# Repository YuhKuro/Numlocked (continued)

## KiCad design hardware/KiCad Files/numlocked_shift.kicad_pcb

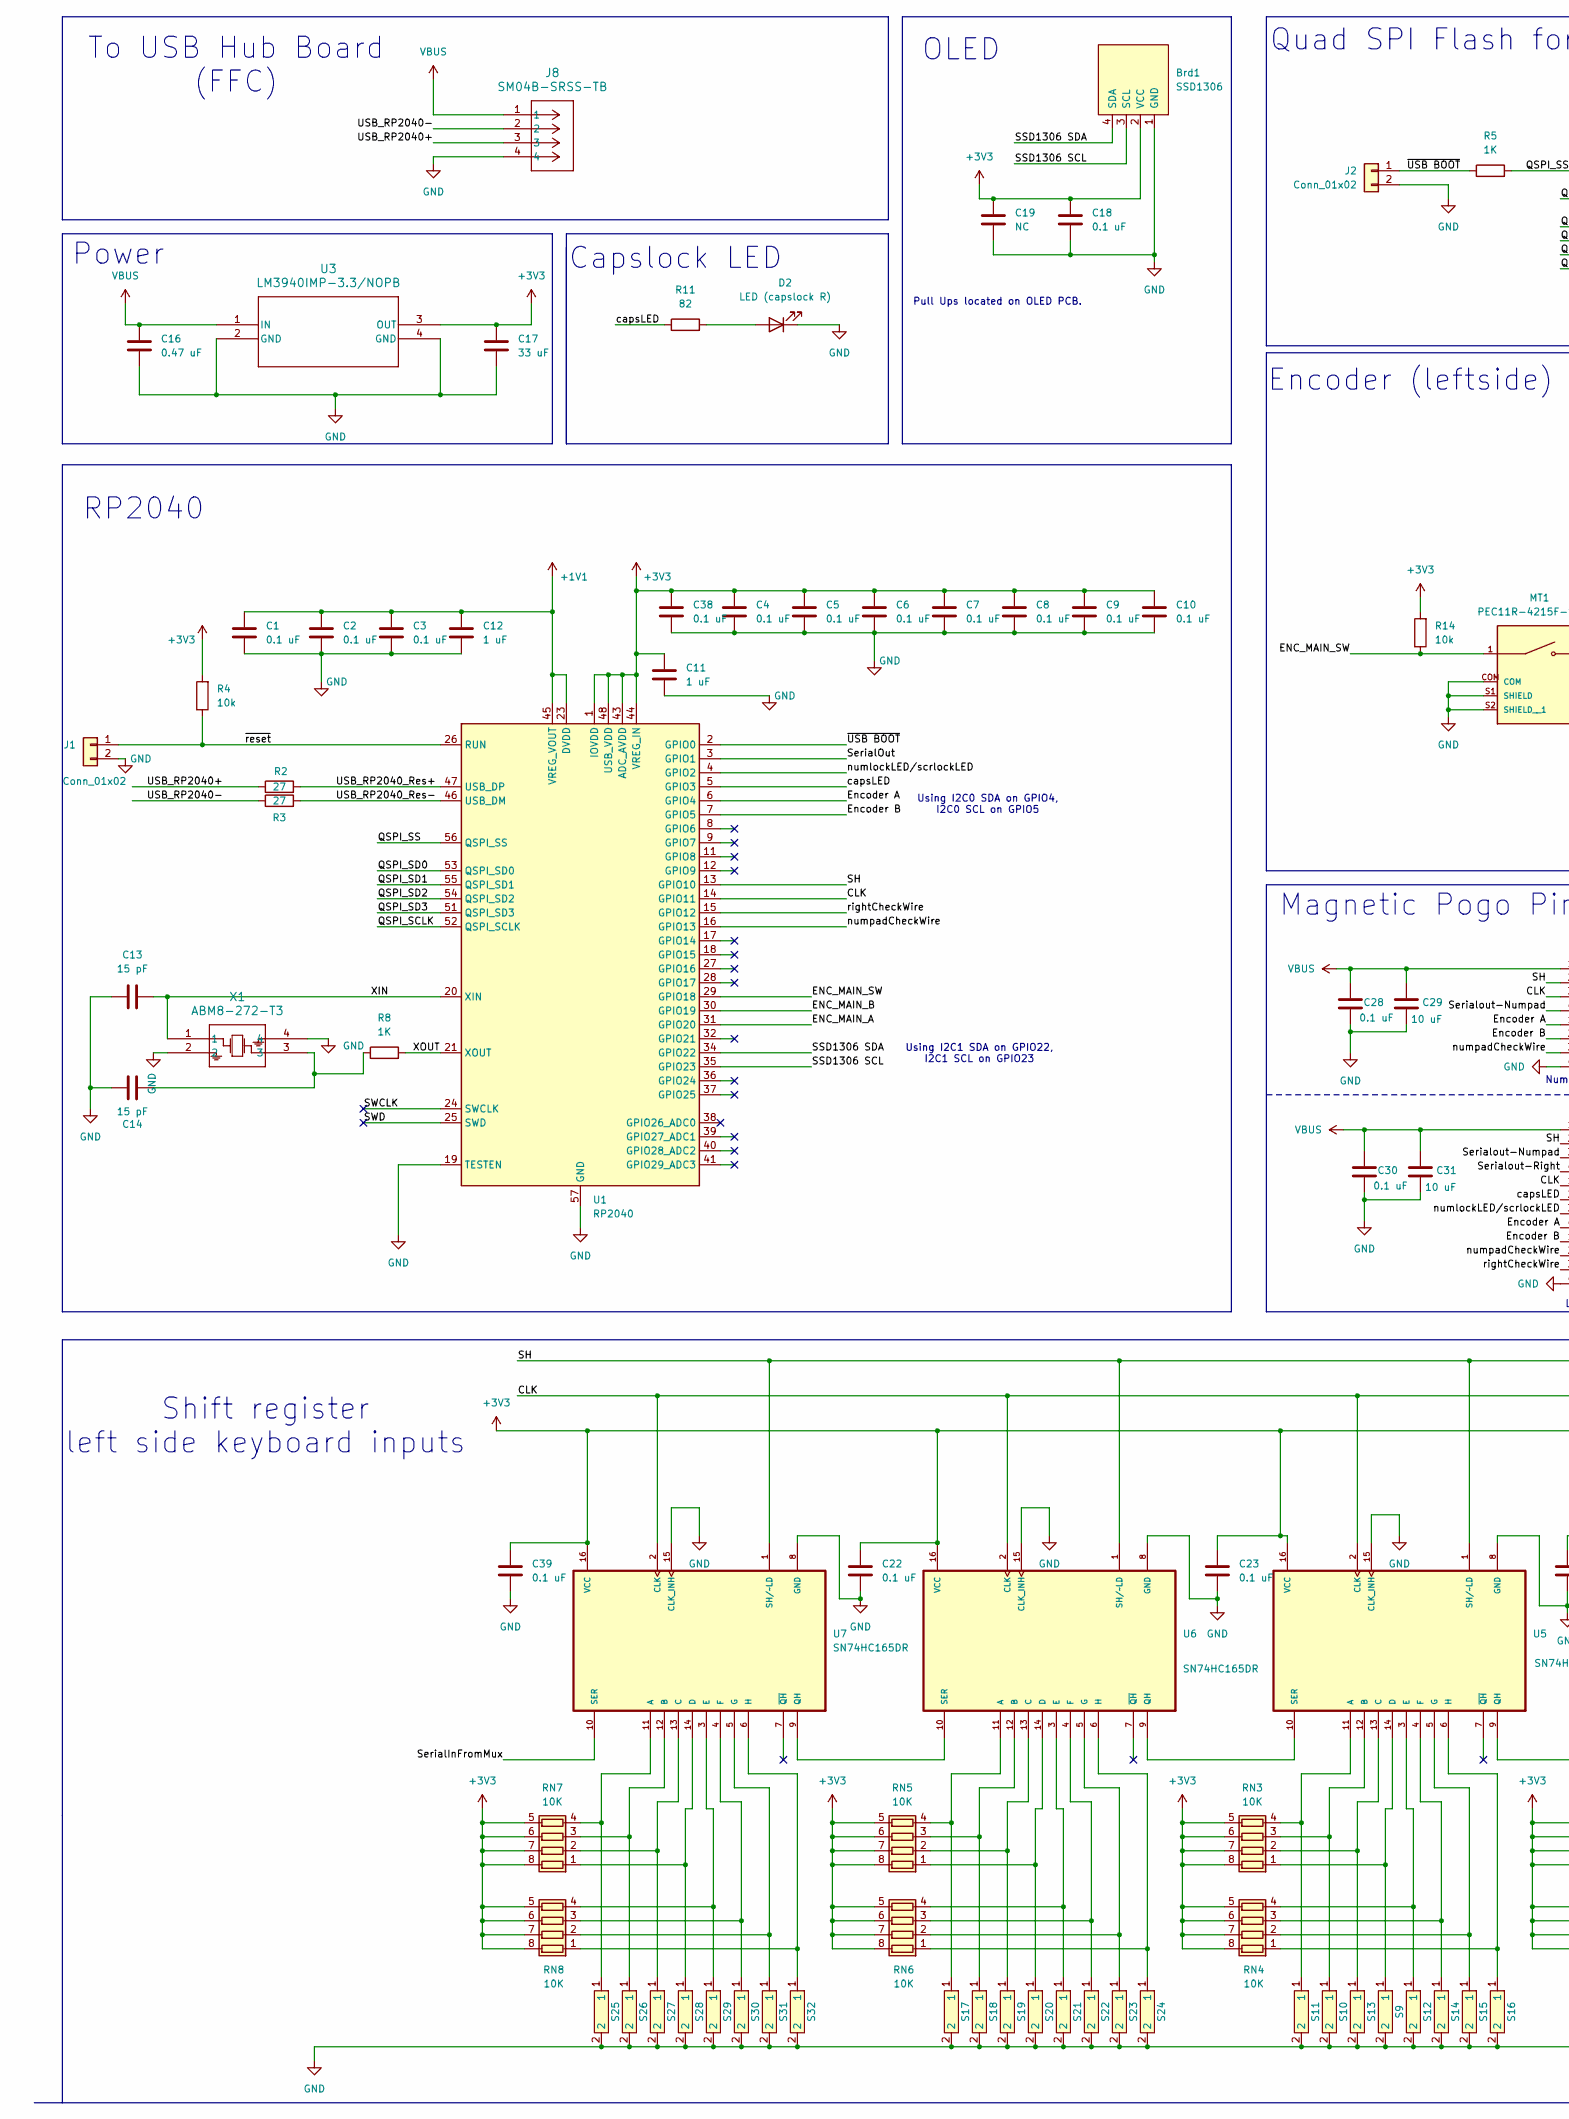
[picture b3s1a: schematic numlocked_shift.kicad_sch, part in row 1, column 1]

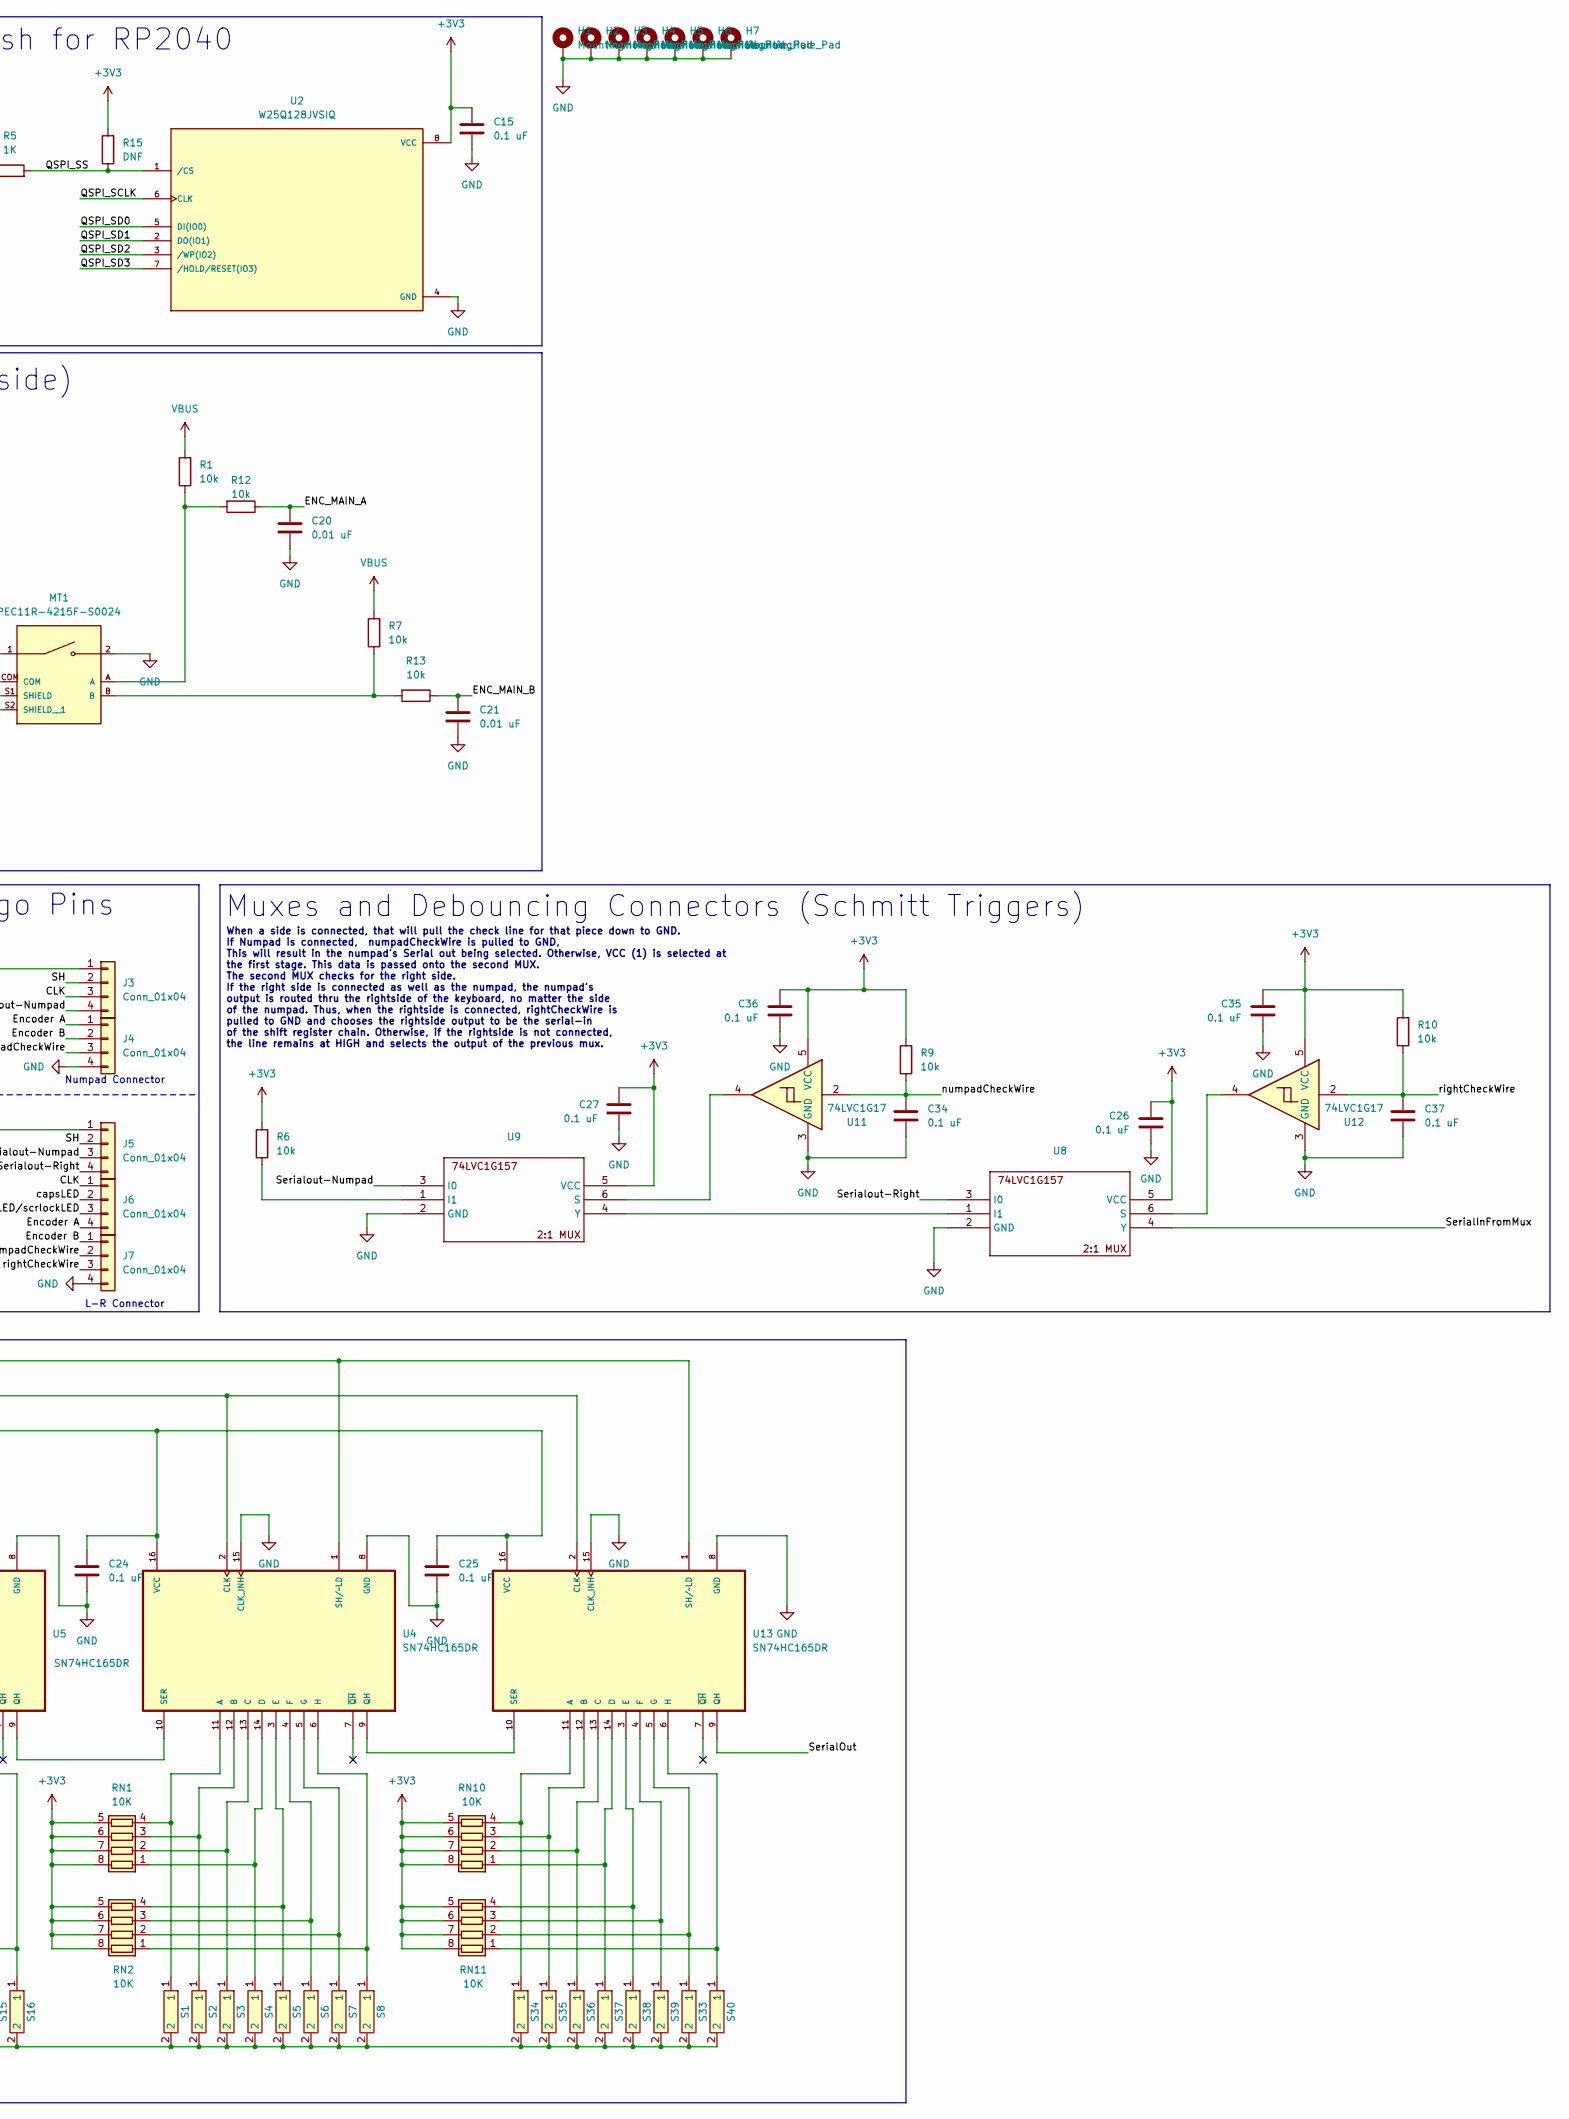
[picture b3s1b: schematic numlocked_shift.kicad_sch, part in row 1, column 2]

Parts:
Brd1: SSD1306; SSD1306-0.91-OLED-4pin-128x32
C1, C2, C3, C4, C5, C6, C7, C8, C9, C10, C18, C22, C23, C24, C25, C26, C27, C28, C30, C34, C35, C36, C37, C38, C39: 0.1 uF; C_0603_1608Metric
C11, C12: 1 uF; C_0603_1608Metric
C13, C14: 15 pF; C_0603_1608Metric
C15: 0.1 uF; C_0603_1608Metric; PARTREV 8/11/2022
C16: 0.47 uF; C_1206_3216Metric
C17: 33 uF; C_1206_3216Metric
C19: NC; C_0603_1608Metric
C20, C21: 0.01 uF; C_0603_1608Metric
C29, C31: 10 uF; C_0603_1608Metric
D2: LED (capslock R); LED_0805_2012Metric_Pad1.15x1.40mm_HandSolder
H1, H2, H3, H4, H5, H6, H7: MountingHole_Pad; MountingHole_2.2mm_M2_Pad
J1, J2: Conn_01x02; PinSocket_1x02_P2.00mm_Vertical
J3, J4, J5, J6, J7: Conn_01x04; Magnetic_Pogo_Pin_4pos
J8: SM04B-SRSS-TB; CONN_SM04B-SRSS-TB_JST
MT1: PEC11R-4215F-S0024; XDCR_PEC11R-4215F-S0024; PARTREV Rev. 09/19
R1, R4, R6, R7, R9, R10, R12, R13, R14: 10k; R_0603_1608Metric
R2, R3: 27; R_0603_1608Metric
R5, R8: 1K; R_0603_1608Metric
R11: 82; R_0603_1608Metric_Pad0.98x0.95mm_HandSolder
R15: DNF; R_0603_1608Metric
RN1, RN2, RN3, RN4, RN5, RN6, RN7, RN8, RN10, RN11: 10K; R_Array_Convex_4x1206
S1, S2, S3, S4, S5, S10, S13, S14, S15, S16, S17, S18, S19, S20, S21, S22, S23, S24, S25, S26, S27, S28, S29, S30, S31, S32, S34, S35, S36, S37, S38, S39, S40: SW_Cherry_Kalih_1.00u
S6: SW_Cherry_Kalih_1.5u
S7: SW_Cherry_Kalih_1.75u
S8: SW_Cherry_Kalih_2.25u
S9, S11, S12: SW_Cherry_Kalih_1.25u
S33: SW_Cherry_Kalih_6.25u
U1: RP2040; QFN-56-1EP_7x7mm_P0.4mm_EP3.2x3.2mm
U2: W25Q128JVSIQ; SOIC127P790X216-8N; PARTREV I
U3: LM3940IMP-3.3/NOPB; SOT-223
U4, U5, U6, U7: SN74HC165DR; SOIC127P600X175-16N
U8, U9: SC-74-6_1.55x2.9mm_P0.95mm
U11, U12: 74LVC1G17; SOT-23-5
U13: SN74HC165DR; SOP-16_3.9x9.9mm_P1.27mm
X1: ABM8-272-T3; Crystal_SMD_Abracon_ABM8AIG-4Pin_3.2x2.5mm

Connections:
+1V1: C1.1, C2.1, C3.1, C12.1, U1.23 (DVDD), U1.45 (VREG_VOUT), U1.50 (DVDD)
+3V3: Brd1.2 (VCC), C4.1, C5.1, C6.1, C7.1, C8.1, C9.1, C10.1, C11.1, C15.1, C17.1, C18.1, C19.1, C22.1, C23.1, C24.1, C25.1, C26.1, C27.1, C35.1, C36.1, C38.1, C39.1, R4.2, R6.2, R9.2, R10.2, R14.2, R15.2, RN1.5 (R4.2), RN1.6 (R3.2), RN1.7 (R2.2), RN1.8 (R1.2), RN2.5 (R4.2), RN2.6 (R3.2), RN2.7 (R2.2), RN2.8 (R1.2), RN3.5 (R4.2), RN3.6 (R3.2), RN3.7 (R2.2), RN3.8 (R1.2), RN4.5 (R4.2), RN4.6 (R3.2), RN4.7 (R2.2), RN4.8 (R1.2), RN5.5 (R4.2), RN5.6 (R3.2), RN5.7 (R2.2), RN5.8 (R1.2), RN6.5 (R4.2), RN6.6 (R3.2), RN6.7 (R2.2), RN6.8 (R1.2), RN7.5 (R4.2), RN7.6 (R3.2), RN7.7 (R2.2), RN7.8 (R1.2), RN8.5 (R4.2), RN8.6 (R3.2), RN8.7 (R2.2), RN8.8 (R1.2), RN10.5 (R4.2), RN10.6 (R3.2), RN10.7 (R2.2), RN10.8 (R1.2), RN11.5 (R4.2), RN11.6 (R3.2), RN11.7 (R2.2), RN11.8 (R1.2), U1.1 (IOVDD), U1.10 (IOVDD), U1.22 (IOVDD), U1.33 (IOVDD), U1.42 (IOVDD), U1.43 (ADC_AVDD), U1.44 (VREG_IN), U1.48 (USB_VDD), U1.49 (IOVDD), U2.8 (VCC), U3.3 (OUT), U4.16 (VCC), U5.16 (VCC), U6.16 (VCC), U7.16 (VCC), U8.5 (VCC), U9.5 (VCC), U11.5 (VCC), U12.5 (VCC), U13.16 (VCC)
/CLK: J3.3, J6.1, U1.14 (GPIO11), U4.2 (CLK), U5.2 (CLK), U6.2 (CLK), U7.2 (CLK), U13.2 (CLK)
/ENC_MAIN_A: C20.1, R12.1, U1.31 (GPIO20)
/ENC_MAIN_B: C21.1, R13.1, U1.30 (GPIO19)
/ENC_MAIN_SW: MT1.1, R14.1, U1.29 (GPIO18)
/Encoder A: J4.1, J6.4, U1.6 (GPIO4)
/Encoder B: J4.2, J7.1, U1.7 (GPIO5)
/QSPI_SCLK: U1.52 (QSPI_SCLK), U2.6 (CLK)
/QSPI_SD0: U1.53 (QSPI_SD0), U2.5 (DI(IO0))
/QSPI_SD1: U1.55 (QSPI_SD1), U2.2 (DO(IO1))
/QSPI_SD2: U1.54 (QSPI_SD2), U2.3 (/WP(IO2))
/QSPI_SD3: U1.51 (QSPI_SD3), U2.7 (/HOLD/RESET(IO3))
/QSPI_SS: R5.2, R15.1, U1.56 (QSPI_SS), U2.1 (/CS)
/SH: J3.2, J5.2, U1.13 (GPIO10), U4.1 (SH/~LD), U5.1 (SH/~LD), U6.1 (SH/~LD), U7.1 (SH/~LD), U13.1 (SH/~LD)
/SSD1306 SCL: Brd1.3 (SCL), U1.35 (GPIO23)
/SSD1306 SDA: Brd1.4 (SDA), U1.34 (GPIO22)
/SWCLK: U1.24 (SWCLK)
/SWD: U1.25 (SWD)
/SerialInFromMux: U7.10 (SER), U8.4 (Y)
/SerialOut: U1.3 (GPIO1), U13.9 (QH)
/Serialout-Numpad: J3.4, J5.3, U9.3 (I0)
/Serialout-Right: J5.4, U8.3 (I0)
/USB_RP2040+: J8.3, R2.1
/USB_RP2040-: J8.2, R3.1
/USB_RP2040_Res+: R2.2, U1.47 (USB_DP)
/USB_RP2040_Res-: R3.2, U1.46 (USB_DM)
/XIN: C13.2, U1.20 (XIN), X1.1
/XOUT: R8.2, U1.21 (XOUT)
/capsLED: J6.2, R11.1, U1.5 (GPIO3)
/numlockLED/scrlockLED: J6.3, U1.4 (GPIO2)
/numpadCheckWire: C34.1, J4.3, J7.2, R9.1, U1.16 (GPIO13), U11.2
/rightCheckWire: C37.1, J7.3, R10.1, U1.15 (GPIO12), U12.2
/~USB BOOT: J2.1, R5.1, U1.2 (GPIO0)
/~reset: J1.1, R4.1, U1.26 (RUN)
GND: Brd1.1 (GND), C1.2, C2.2, C3.2, C4.2, C5.2, C6.2, C7.2, C8.2, C9.2, C10.2, C11.2, C12.2, C13.1, C14.1, C15.2, C16.2, C17.2, C18.2, C19.2, C20.2, C21.2, C22.2, C23.2, C24.2, C25.2, C26.2, C27.2, C28.2, C29.2, C30.2, C31.2, C34.2, C35.2, C36.2, C37.2, C38.2, C39.2, D2.1 (K), H1.1, H2.1, H3.1, H4.1, H5.1, H6.1, H7.1, J1.2, J2.2, J4.4, J7.4, J8.4, MT1.2, MT1.COM, MT1.S1 (SHIELD), MT1.S2 (SHIELD__1), S1.2, S2.2, S3.2, S4.2, S5.2, S6.2, S7.2, S8.2, S9.2, S10.2, S11.2, S12.2, S13.2, S14.2, S15.2, S16.2, S17.2, S18.2, S19.2, S20.2, S21.2, S22.2, S23.2, S24.2, S25.2, S26.2, S27.2, S28.2, S29.2, S30.2, S31.2, S32.2, S33.2, S34.2, S35.2, S36.2, S37.2, S38.2, S39.2, S40.2, U1.19 (TESTEN), U1.57 (GND), U2.4 (GND), U3.2 (GND), U3.4 (GND), U4.8 (GND), U4.15 (CLK_INH), U5.8 (GND), U5.15 (CLK_INH), U6.8 (GND), U6.15 (CLK_INH), U7.8 (GND), U7.15 (CLK_INH), U8.2 (GND), U9.2 (GND), U11.3 (GND), U12.3 (GND), U13.8 (GND), U13.15 (CLK_INH), X1.2, X1.4
unnamed: C14.2, R8.1, X1.3
unnamed: D2.2 (A), R11.2
unnamed: MT1.A, R1.1, R12.2
unnamed: MT1.B, R7.1, R13.2
unnamed: RN1.1 (R1.1), S4.1, U4.14 (D)
unnamed: RN1.2 (R2.1), S3.1, U4.13 (C)
unnamed: RN1.3 (R3.1), S2.1, U4.12 (B)
unnamed: RN1.4 (R4.1), S1.1, U4.11 (A)
unnamed: RN2.1 (R1.1), S8.1, U4.6 (H)
unnamed: RN2.2 (R2.1), S7.1, U4.5 (G)
unnamed: RN2.3 (R3.1), S6.1, U4.4 (F)
unnamed: RN2.4 (R4.1), S5.1, U4.3 (E)
unnamed: RN3.1 (R1.1), S9.1, U5.14 (D)
unnamed: RN3.2 (R2.1), S13.1, U5.13 (C)
unnamed: RN3.3 (R3.1), S10.1, U5.12 (B)
unnamed: RN3.4 (R4.1), S11.1, U5.11 (A)
unnamed: RN4.1 (R1.1), S16.1, U5.6 (H)
unnamed: RN4.2 (R2.1), S15.1, U5.5 (G)
unnamed: RN4.3 (R3.1), S14.1, U5.4 (F)
unnamed: RN4.4 (R4.1), S12.1, U5.3 (E)
unnamed: RN5.1 (R1.1), S20.1, U6.14 (D)
unnamed: RN5.2 (R2.1), S19.1, U6.13 (C)
unnamed: RN5.3 (R3.1), S18.1, U6.12 (B)
unnamed: RN5.4 (R4.1), S17.1, U6.11 (A)
unnamed: RN6.1 (R1.1), S24.1, U6.6 (H)
unnamed: RN6.2 (R2.1), S23.1, U6.5 (G)
unnamed: RN6.3 (R3.1), S22.1, U6.4 (F)
unnamed: RN6.4 (R4.1), S21.1, U6.3 (E)
unnamed: RN7.1 (R1.1), S28.1, U7.14 (D)
unnamed: RN7.2 (R2.1), S27.1, U7.13 (C)
unnamed: RN7.3 (R3.1), S26.1, U7.12 (B)
unnamed: RN7.4 (R4.1), S25.1, U7.11 (A)
unnamed: RN8.1 (R1.1), S32.1, U7.6 (H)
unnamed: RN8.2 (R2.1), S31.1, U7.5 (G)
unnamed: RN8.3 (R3.1), S30.1, U7.4 (F)
unnamed: RN8.4 (R4.1), S29.1, U7.3 (E)
unnamed: RN10.1 (R1.1), S37.1, U13.14 (D)
unnamed: RN10.2 (R2.1), S36.1, U13.13 (C)
unnamed: RN10.3 (R3.1), S35.1, U13.12 (B)
unnamed: RN10.4 (R4.1), S34.1, U13.11 (A)
unnamed: RN11.1 (R1.1), S40.1, U13.6 (H)
unnamed: RN11.2 (R2.1), S33.1, U13.5 (G)
unnamed: RN11.3 (R3.1), S39.1, U13.4 (F)
unnamed: RN11.4 (R4.1), S38.1, U13.3 (E)
unnamed: U4.10 (SER), U5.9 (QH)
unnamed: U5.10 (SER), U6.9 (QH)
unnamed: U6.10 (SER), U7.9 (QH)
unnamed: U8.1 (I1), U9.4 (Y)
unnamed: U8.6 (S), U12.4
unnamed: R6.1, U9.1 (I1)
unnamed: U9.6 (S), U11.4
unnamed: U4.9 (QH), U13.10 (SER)
VBUS: C16.1, C28.1, C29.1, C30.1, C31.1, J3.1, J5.1, J8.1, R1.2, R7.2, U3.1 (IN)

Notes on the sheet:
When a side is connected, that will pull the check line for that piece down to GND. If Numpad is connected, numpadCheckWire is pulled to GND, This will result in the numpad's Serial out being selected. Otherwise, VCC (1) is selected at the first stage. This data is passed onto the second MUX. The s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
Power
L-R Connector
Using I2C1 SDA on GPIO22, I2C1 SCL on GPIO23
Quad SPI Flash for RP2040
Muxes and Debouncing Connectors (Schmitt Triggers)
Using I2C0 SDA on GPIO4, I2C0 SCL on GPIO5
Numpad Connector
OLED
Capslock LED
Pull Ups located on OLED PCB.
Shift register left side keyboard inputs
RP2040
Encoder (leftside)
To USB Hub Board (FFC)
Magnetic Pogo Pins

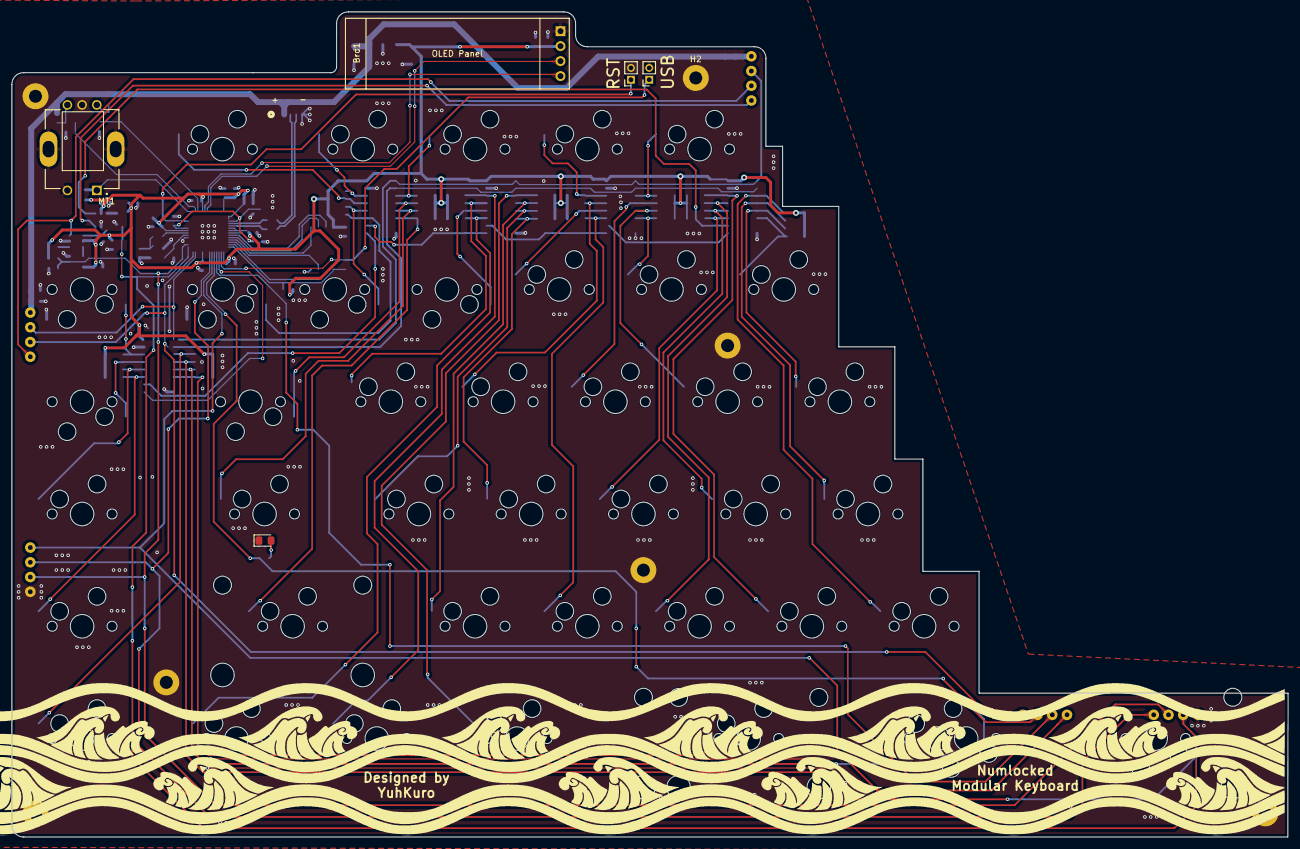
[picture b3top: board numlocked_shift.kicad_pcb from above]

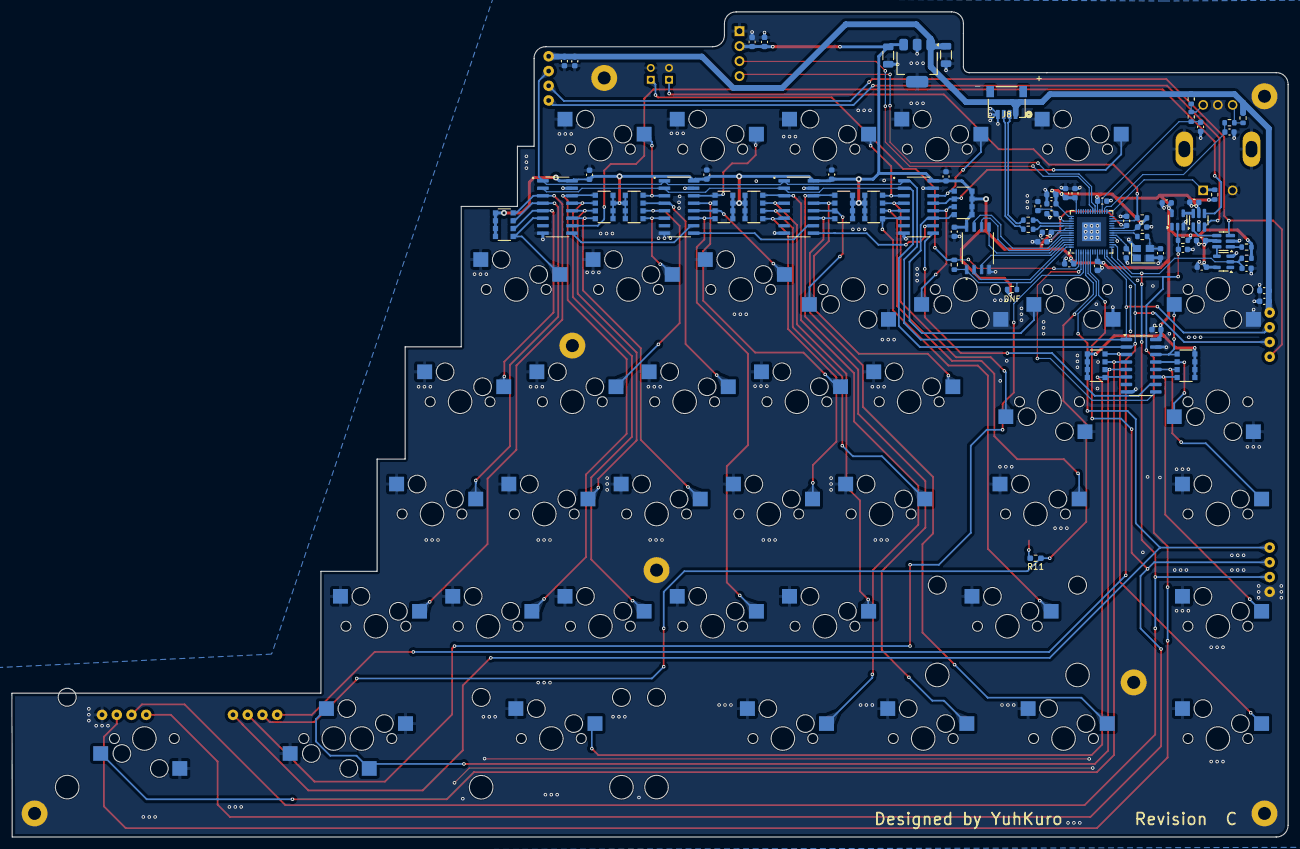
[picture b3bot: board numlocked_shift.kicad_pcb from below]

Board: 4 copper layers, 216.5 x 140.0 mm, 133 parts (78 on the bottom side), 87 nets.

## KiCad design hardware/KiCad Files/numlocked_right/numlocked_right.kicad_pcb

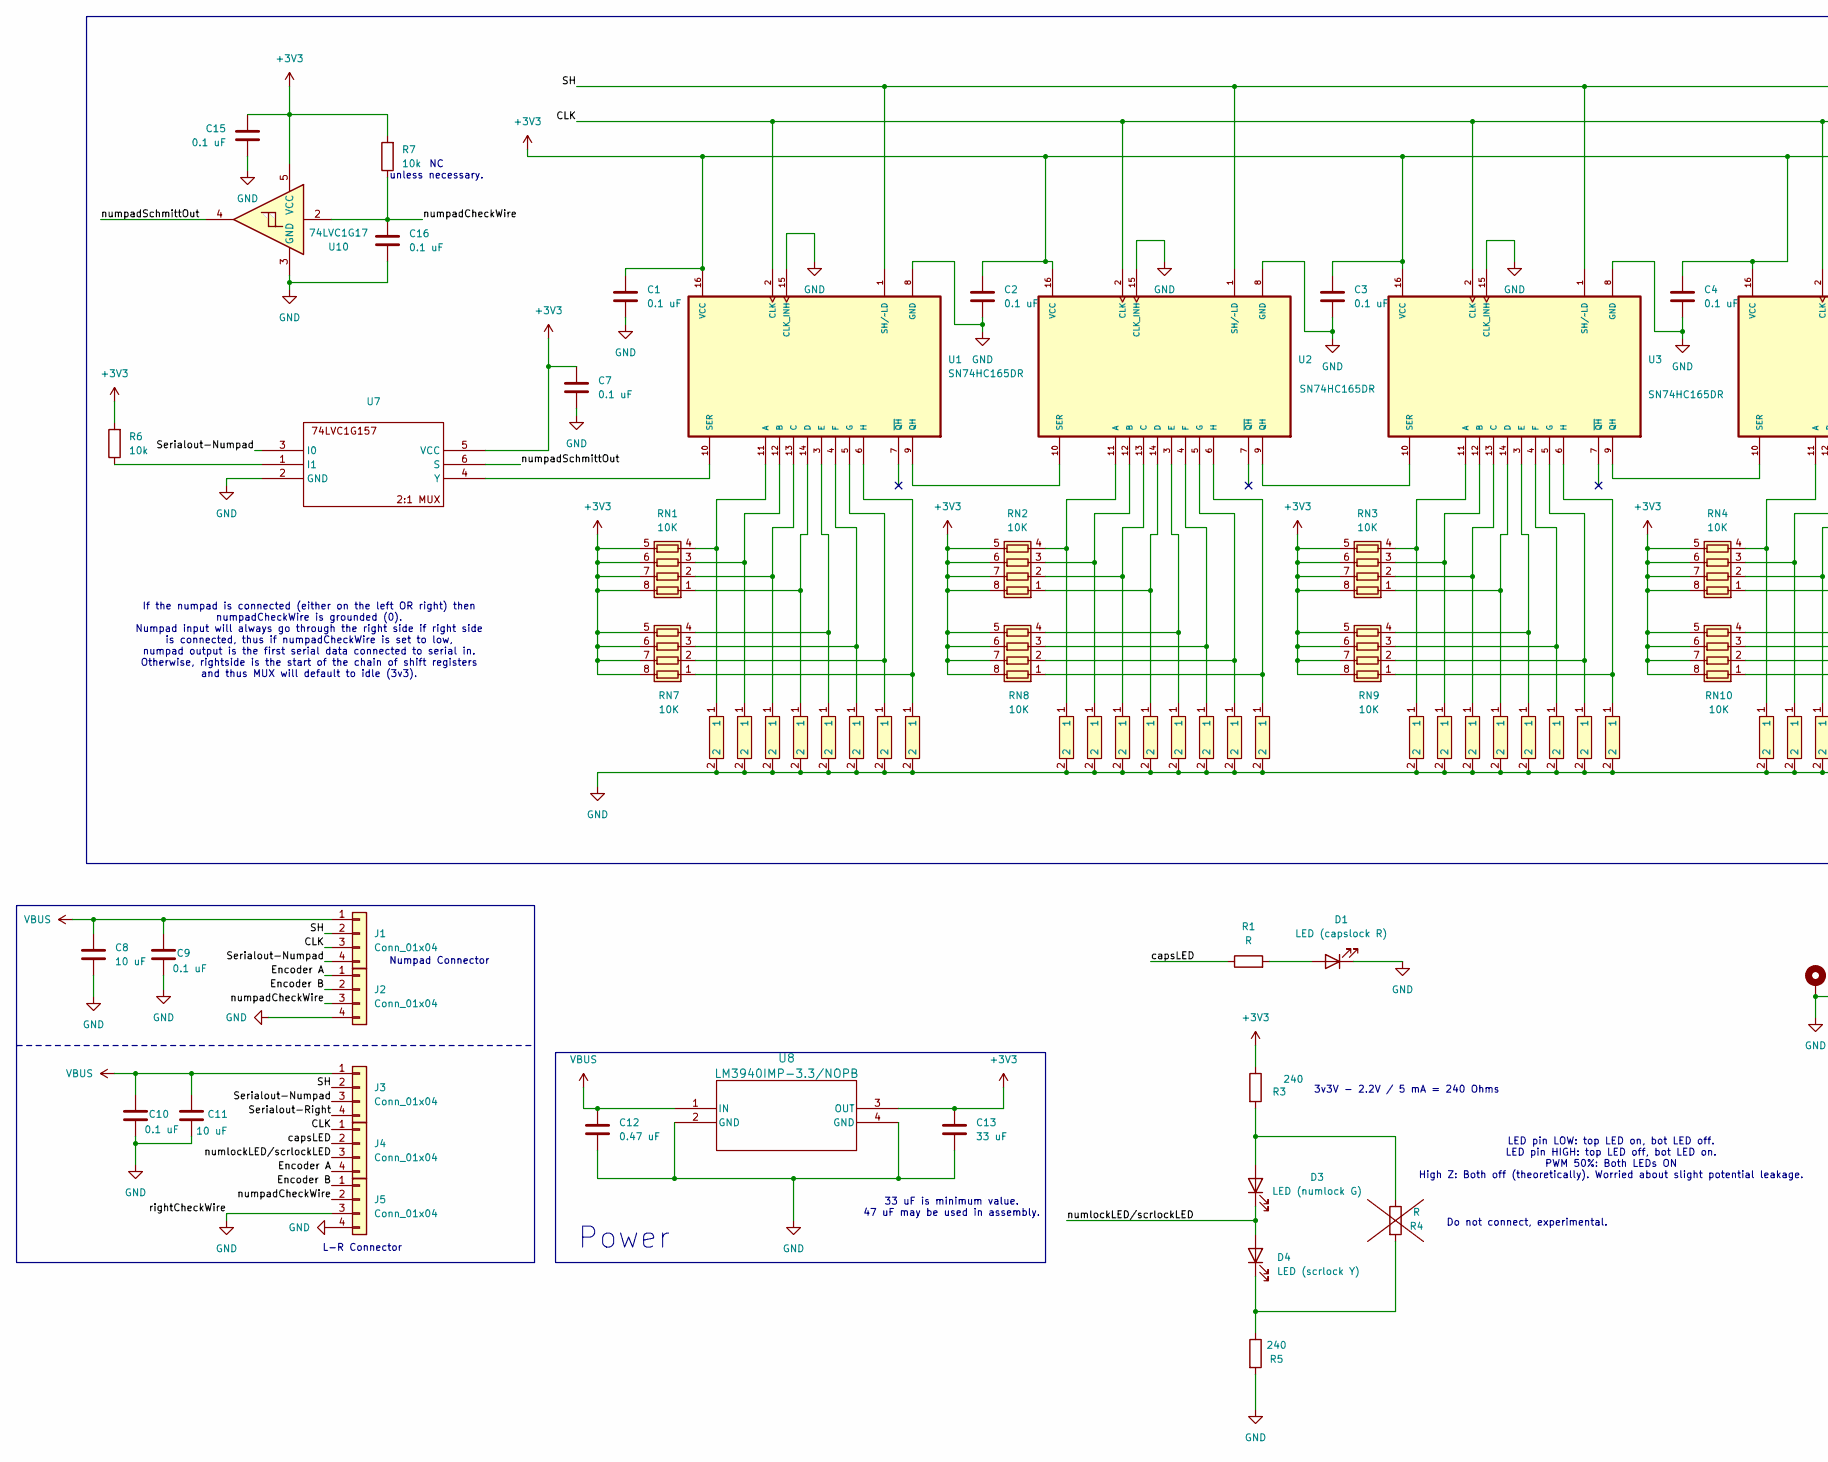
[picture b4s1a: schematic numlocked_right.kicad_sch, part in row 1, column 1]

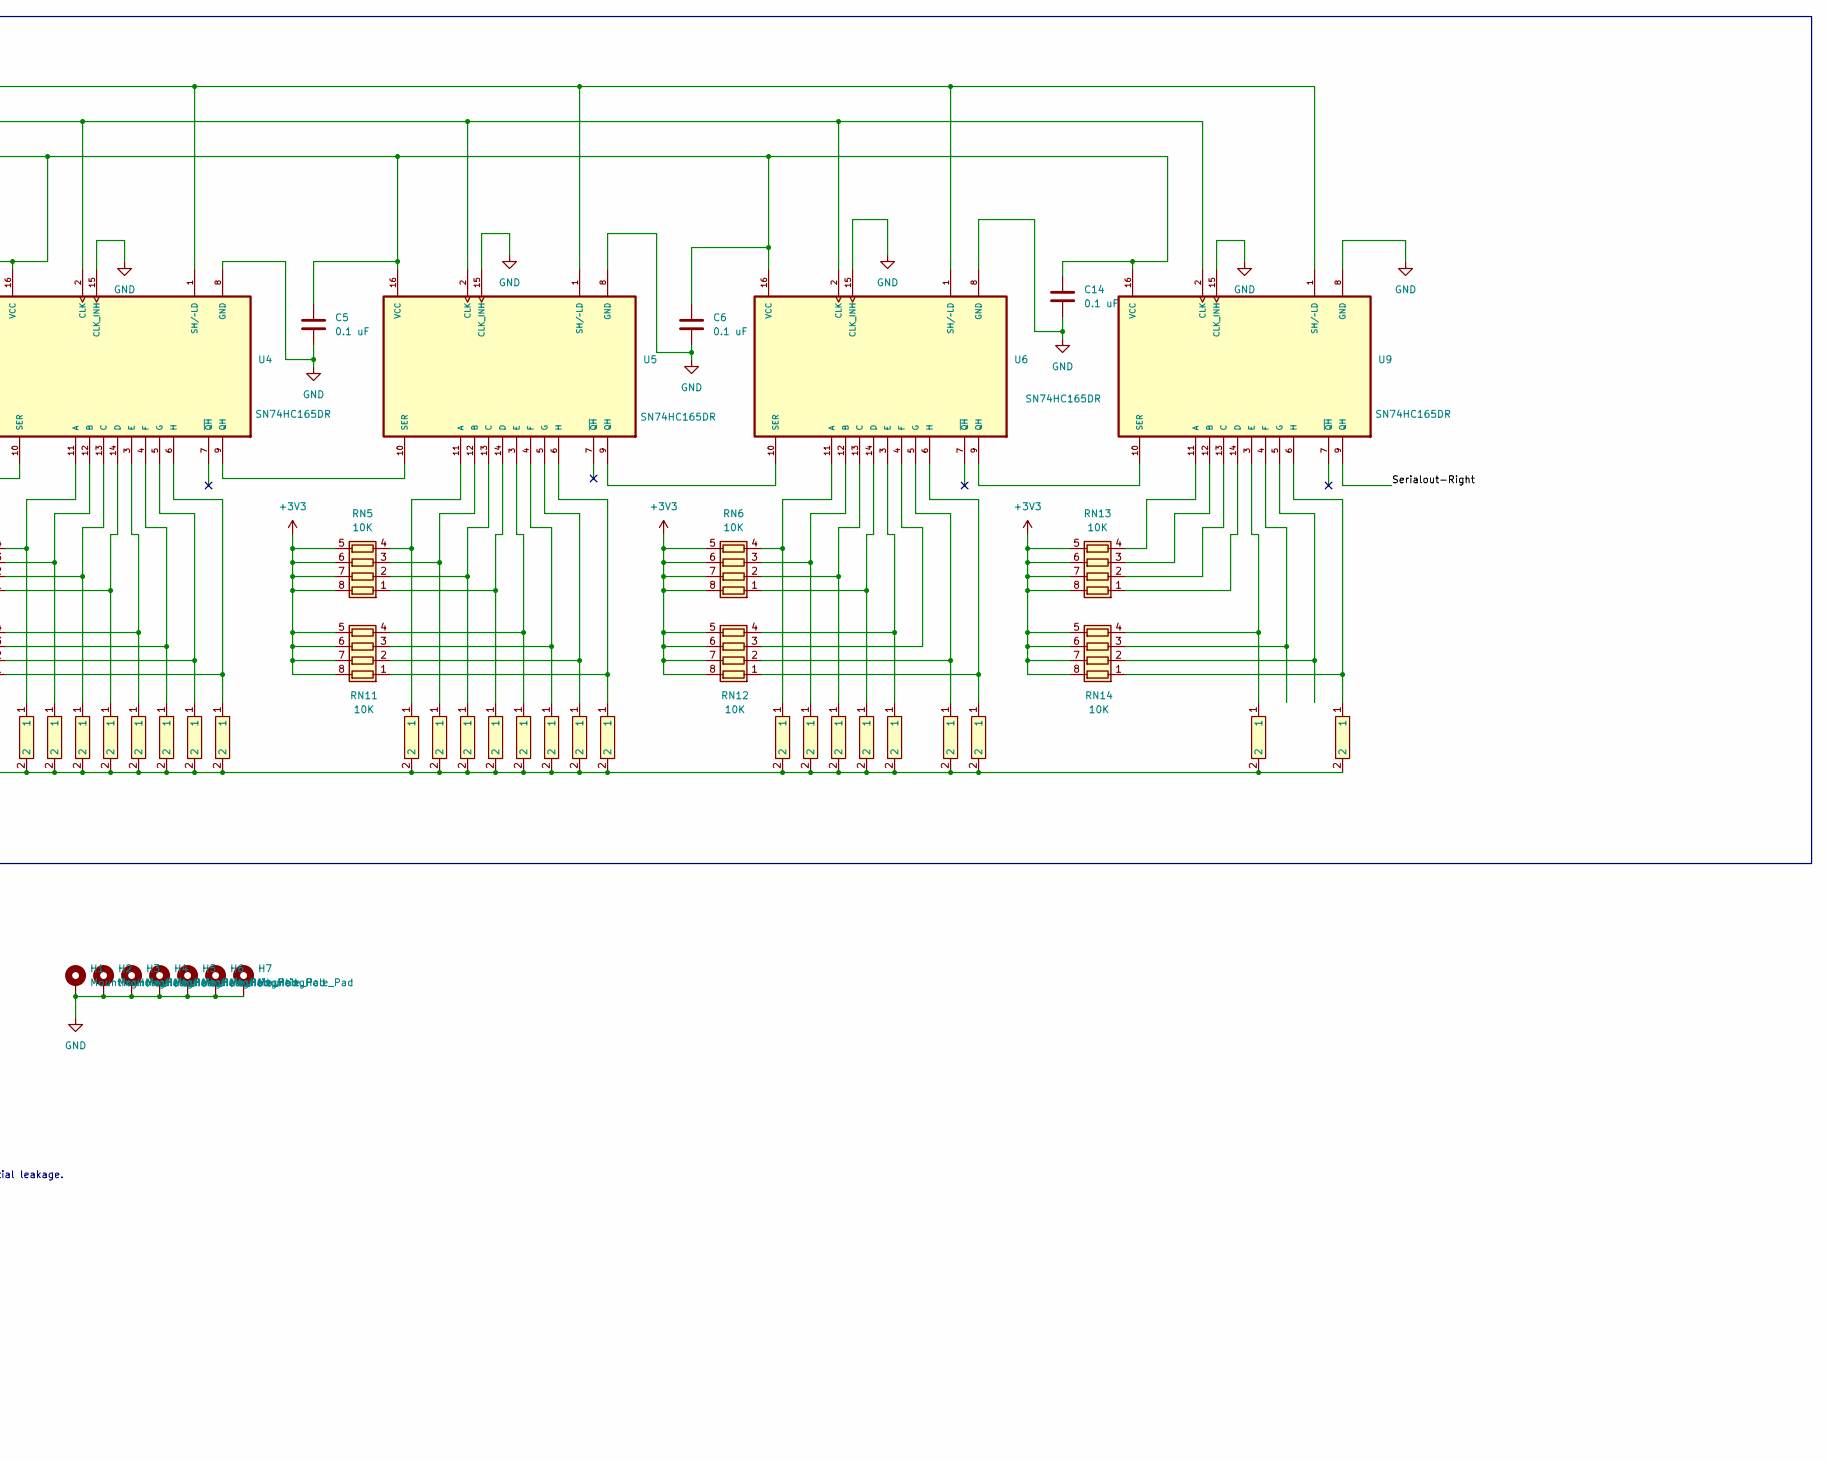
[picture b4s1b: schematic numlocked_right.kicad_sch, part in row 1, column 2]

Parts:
C1, C2, C3, C4, C5, C6, C7, C9, C10, C14, C15, C16: 0.1 uF; C_0603_1608Metric
C8, C11: 10 uF; C_0603_1608Metric
C12: 0.47 uF; C_1206_3216Metric
C13: 33 uF; C_1206_3216Metric
D1: LED (capslock R); LED_0805_2012Metric
D3: LED (numlock G); LED_0805_2012Metric
D4: LED (scrlock Y); LED_0805_2012Metric
H1, H2, H3, H4, H5, H6, H7: MountingHole_Pad; MountingHole_2.2mm_M2_Pad
J1, J2, J3, J4, J5: Conn_01x04; Magnetic_Pogo_Pin_4pos
R1, R4: R; R_0603_1608Metric
R3, R5: 240; R_0603_1608Metric
R6, R7: 10k; R_0603_1608Metric
RN1, RN2, RN3, RN4, RN5, RN6, RN7, RN8, RN9, RN10, RN11, RN12, RN13, RN14: 10K; R_Array_Convex_4x1206
S1, S2, S3, S4, S5, S6, S7, S8, S9, S10, S11, S12, S13, S14, S15, S16, S17, S18, S19, S20, S21, S22, S23, S24, S25, S26, S27, S28, S29, S30, S31, S32, S33, S34, S36, S39, S40, S41, S43, S44, S45, S46, S47, S48, S49: SW_Cherry_Kalih_1.00u
S35, S38: SW_Cherry_Kalih_1.75u
S37: SW_Cherry_Kalih_2.25u
S42: SW_Cherry_Kalih_2.00u
U1, U2, U3, U4, U5, U6, U9: SN74HC165DR; SOIC127P600X175-16N
U7: SC-74-6_1.55x2.9mm_P0.95mm
U8: LM3940IMP-3.3/NOPB; SOT-223
U10: 74LVC1G17; SOT-23-5

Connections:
+3V3: C1.1, C2.1, C3.1, C4.1, C5.1, C6.1, C7.1, C13.1, C14.1, C15.1, R3.1, R6.2, R7.2, RN1.5 (R4.2), RN1.6 (R3.2), RN1.7 (R2.2), RN1.8 (R1.2), RN2.5 (R4.2), RN2.6 (R3.2), RN2.7 (R2.2), RN2.8 (R1.2), RN3.5 (R4.2), RN3.6 (R3.2), RN3.7 (R2.2), RN3.8 (R1.2), RN4.5 (R4.2), RN4.6 (R3.2), RN4.7 (R2.2), RN4.8 (R1.2), RN5.5 (R4.2), RN5.6 (R3.2), RN5.7 (R2.2), RN5.8 (R1.2), RN6.5 (R4.2), RN6.6 (R3.2), RN6.7 (R2.2), RN6.8 (R1.2), RN7.5 (R4.2), RN7.6 (R3.2), RN7.7 (R2.2), RN7.8 (R1.2), RN8.5 (R4.2), RN8.6 (R3.2), RN8.7 (R2.2), RN8.8 (R1.2), RN9.5 (R4.2), RN9.6 (R3.2), RN9.7 (R2.2), RN9.8 (R1.2), RN10.5 (R4.2), RN10.6 (R3.2), RN10.7 (R2.2), RN10.8 (R1.2), RN11.5 (R4.2), RN11.6 (R3.2), RN11.7 (R2.2), RN11.8 (R1.2), RN12.5 (R4.2), RN12.6 (R3.2), RN12.7 (R2.2), RN12.8 (R1.2), RN13.5 (R4.2), RN13.6 (R3.2), RN13.7 (R2.2), RN13.8 (R1.2), RN14.5 (R4.2), RN14.6 (R3.2), RN14.7 (R2.2), RN14.8 (R1.2), U1.16 (VCC), U2.16 (VCC), U3.16 (VCC), U4.16 (VCC), U5.16 (VCC), U6.16 (VCC), U7.5 (VCC), U8.3 (OUT), U9.16 (VCC), U10.5 (VCC)
/CLK: J1.3, J4.1, U1.2 (CLK), U2.2 (CLK), U3.2 (CLK), U4.2 (CLK), U5.2 (CLK), U6.2 (CLK), U9.2 (CLK)
/Encoder A: J2.1, J4.4
/Encoder B: J2.2, J5.1
/SH: J1.2, J3.2, U1.1 (SH/~LD), U2.1 (SH/~LD), U3.1 (SH/~LD), U4.1 (SH/~LD), U5.1 (SH/~LD), U6.1 (SH/~LD), U9.1 (SH/~LD)
/Serialout-Numpad: J1.4, J3.3, U7.3 (I0)
/Serialout-Right: J3.4, U9.9 (QH)
/capsLED: J4.2, R1.1
/numlockLED/scrlockLED: D3.1 (K), D4.2 (A), J4.3
/numpadCheckWire: C16.1, J2.3, J5.2, R7.1, U10.2
/numpadSchmittOut: U7.6 (S), U10.4
GND: C1.2, C2.2, C3.2, C4.2, C5.2, C6.2, C7.2, C8.2, C9.2, C10.2, C11.2, C12.2, C13.2, C14.2, C15.2, C16.2, D1.1 (K), H1.1, H2.1, H3.1, H4.1, H5.1, H6.1, H7.1, J2.4, J5.3, J5.4, R5.2, S1.2, S2.2, S3.2, S4.2, S5.2, S6.2, S7.2, S8.2, S9.2, S10.2, S11.2, S12.2, S13.2, S14.2, S15.2, S16.2, S17.2, S18.2, S19.2, S20.2, S21.2, S22.2, S23.2, S24.2, S25.2, S26.2, S27.2, S28.2, S29.2, S30.2, S31.2, S32.2, S33.2, S34.2, S35.2, S36.2, S37.2, S38.2, S39.2, S40.2, S41.2, S42.2, S43.2, S44.2, S45.2, S46.2, S47.2, S48.2, S49.2, U1.8 (GND), U1.15 (CLK_INH), U2.8 (GND), U2.15 (CLK_INH), U3.8 (GND), U3.15 (CLK_INH), U4.8 (GND), U4.15 (CLK_INH), U5.8 (GND), U5.15 (CLK_INH), U6.8 (GND), U6.15 (CLK_INH), U7.2 (GND), U8.2 (GND), U8.4 (GND), U9.8 (GND), U9.15 (CLK_INH), U10.3 (GND)
unnamed: D1.2 (A), R1.2
unnamed: D3.2 (A), R3.2, R4.1
unnamed: D4.1 (K), R4.2, R5.1
unnamed: RN1.1 (R1.1), S4.1, U1.14 (D)
unnamed: RN1.2 (R2.1), S3.1, U1.13 (C)
unnamed: RN1.3 (R3.1), S2.1, U1.12 (B)
unnamed: RN1.4 (R4.1), S1.1, U1.11 (A)
unnamed: RN2.1 (R1.1), S12.1, U2.14 (D)
unnamed: RN2.2 (R2.1), S11.1, U2.13 (C)
unnamed: RN2.3 (R3.1), S10.1, U2.12 (B)
unnamed: RN2.4 (R4.1), S9.1, U2.11 (A)
unnamed: RN3.1 (R1.1), S20.1, U3.14 (D)
unnamed: RN3.2 (R2.1), S19.1, U3.13 (C)
unnamed: RN3.3 (R3.1), S18.1, U3.12 (B)
unnamed: RN3.4 (R4.1), S17.1, U3.11 (A)
unnamed: RN4.1 (R1.1), S28.1, U4.14 (D)
unnamed: RN4.2 (R2.1), S27.1, U4.13 (C)
unnamed: RN4.3 (R3.1), S26.1, U4.12 (B)
unnamed: RN4.4 (R4.1), S25.1, U4.11 (A)
unnamed: RN5.1 (R1.1), S36.1, U5.14 (D)
unnamed: RN5.2 (R2.1), S35.1, U5.13 (C)
unnamed: RN5.3 (R3.1), S34.1, U5.12 (B)
unnamed: RN5.4 (R4.1), S33.1, U5.11 (A)
unnamed: RN6.1 (R1.1), S44.1, U6.14 (D)
unnamed: RN6.2 (R2.1), S43.1, U6.13 (C)
unnamed: RN6.3 (R3.1), S42.1, U6.12 (B)
unnamed: RN6.4 (R4.1), S41.1, U6.11 (A)
unnamed: RN7.1 (R1.1), S8.1, U1.6 (H)
unnamed: RN7.2 (R2.1), S7.1, U1.5 (G)
unnamed: RN7.3 (R3.1), S6.1, U1.4 (F)
unnamed: RN7.4 (R4.1), S5.1, U1.3 (E)
unnamed: RN8.1 (R1.1), S16.1, U2.6 (H)
unnamed: RN8.2 (R2.1), S15.1, U2.5 (G)
unnamed: RN8.3 (R3.1), S14.1, U2.4 (F)
unnamed: RN8.4 (R4.1), S13.1, U2.3 (E)
unnamed: RN9.1 (R1.1), S24.1, U3.6 (H)
unnamed: RN9.2 (R2.1), S23.1, U3.5 (G)
unnamed: RN9.3 (R3.1), S22.1, U3.4 (F)
unnamed: RN9.4 (R4.1), S21.1, U3.3 (E)
unnamed: RN10.1 (R1.1), S32.1, U4.6 (H)
unnamed: RN10.2 (R2.1), S31.1, U4.5 (G)
unnamed: RN10.3 (R3.1), S30.1, U4.4 (F)
unnamed: RN10.4 (R4.1), S29.1, U4.3 (E)
unnamed: RN11.1 (R1.1), S40.1, U5.6 (H)
unnamed: RN11.2 (R2.1), S39.1, U5.5 (G)
unnamed: RN11.3 (R3.1), S38.1, U5.4 (F)
unnamed: RN11.4 (R4.1), S37.1, U5.3 (E)
unnamed: RN12.1 (R1.1), S48.1, U6.6 (H)
unnamed: RN12.2 (R2.1), S47.1, U6.5 (G)
unnamed: RN12.3 (R3.1), U6.4 (F)
unnamed: RN12.4 (R4.1), S45.1, U6.3 (E)
unnamed: RN13.1 (R1.1), U9.14 (D)
unnamed: RN13.2 (R2.1), U9.13 (C)
unnamed: RN13.3 (R3.1), U9.12 (B)
unnamed: RN13.4 (R4.1), U9.11 (A)
unnamed: RN14.1 (R1.1), S49.1, U9.6 (H)
unnamed: RN14.2 (R2.1), U9.5 (G)
unnamed: RN14.3 (R3.1), U9.4 (F)
unnamed: RN14.4 (R4.1), S46.1, U9.3 (E)
unnamed: U1.9 (QH), U2.10 (SER)
unnamed: U1.10 (SER), U7.4 (Y)
unnamed: U2.9 (QH), U3.10 (SER)
unnamed: U3.9 (QH), U4.10 (SER)
unnamed: U4.9 (QH), U5.10 (SER)
unnamed: U5.9 (QH), U6.10 (SER)
unnamed: U6.9 (QH), U9.10 (SER)
unnamed: R6.1, U7.1 (I1)
VBUS: C8.1, C9.1, C10.1, C11.1, C12.1, J1.1, J3.1, U8.1 (IN)

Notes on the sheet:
NC unless necessary.
Numpad Connector
33 uF is minimum value. 47 uF may be used in assembly.
Power
If the numpad is connected (either on the left OR right) then numpadCheckWire is grounded (0). Numpad input will always go through the right side if right side is connected, thus if numpadCheckWire is set to low, numpad output is the first serial data connected to serial in. Otherwise, rightside is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
Do not connect, experimental.
LED pin LOW: top LED on, bot LED off. LED pin HIGH: top LED off, bot LED on. PWM 50%: Both LEDs ON High Z: Both off (theoretically). Worried about slight potential leakage.
3v3V - 2.2V / 5 mA = 240 Ohms
L-R Connector
